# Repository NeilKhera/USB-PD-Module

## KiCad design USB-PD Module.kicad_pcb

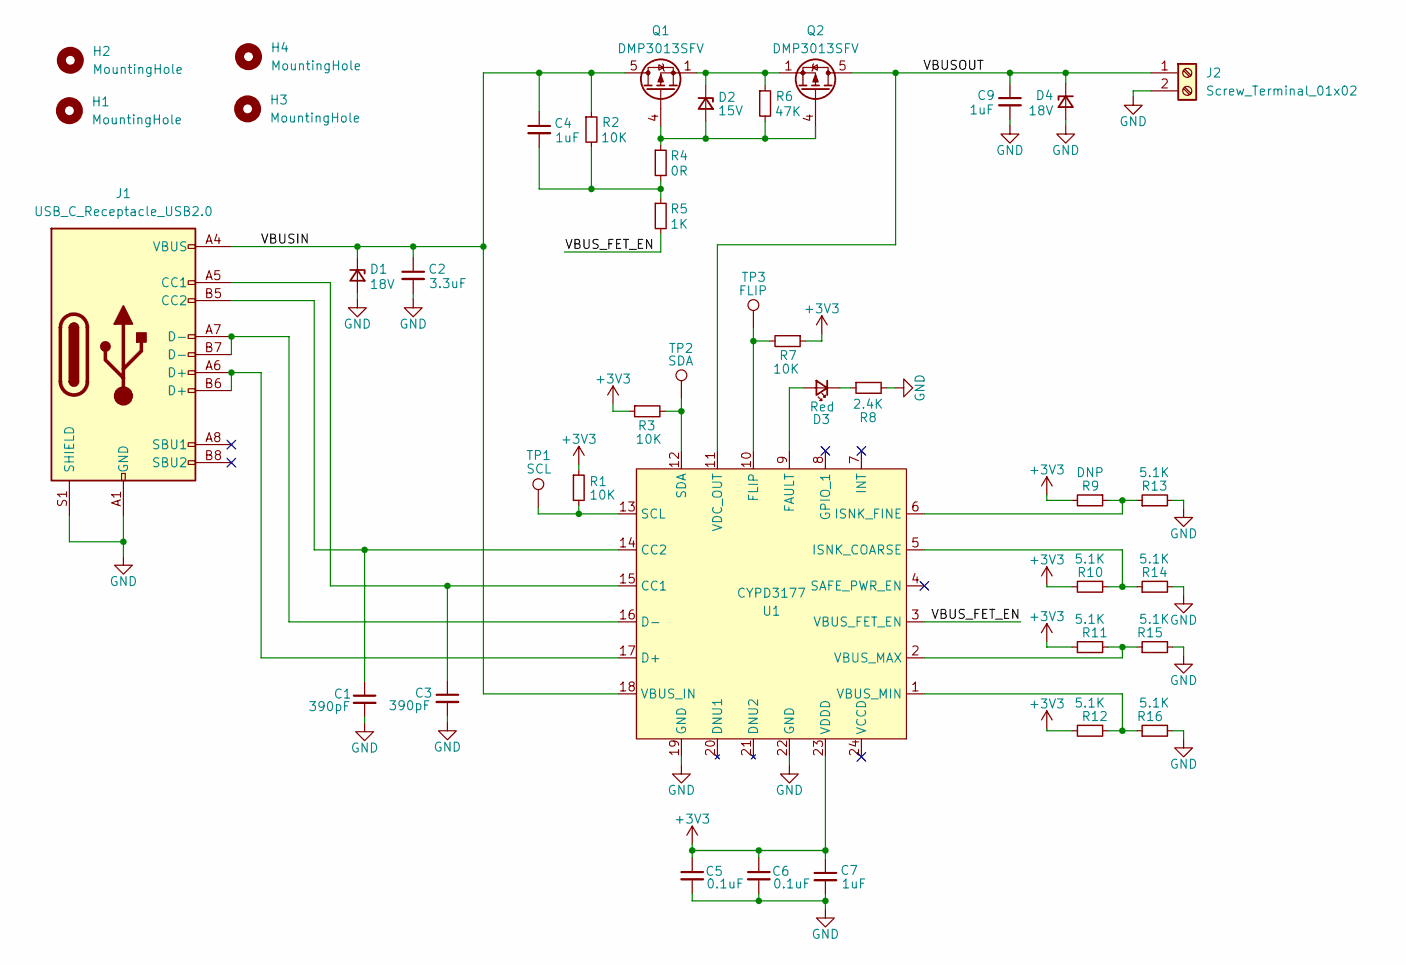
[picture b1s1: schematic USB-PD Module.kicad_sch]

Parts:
C1, C3: 390pF; C_0603_1608Metric
C2: 3.3uF; C_0805_2012Metric
C4, C7: 1uF; C_0603_1608Metric
C5, C6: 0.1uF; C_0603_1608Metric
C9: 1uF; C_0805_2012Metric
D1, D4: 18V; D_SOD-123
D2: 15V; D_SOD-123
D3: Red; LED_0603_1608Metric
H1, H2, H3, H4: MountingHole; MountingHole_2.2mm_M2
J1: USB_C_Receptacle_USB2.0; USB_C_Receptacle_HRO_TYPE-C-31-M-12
J2: Screw_Terminal_01x02; PinHeader_2x01_P2.54mm_Vertical
Q1, Q2: DMP3013SFV; Diodes_PowerDI3333-8
R1, R2, R3, R7: 10K; R_0603_1608Metric
R4: 0R; R_0603_1608Metric
R5: 1K; R_0603_1608Metric
R6: 47K; R_0603_1608Metric
R8: 2.4K; R_0603_1608Metric
R9: DNP; R_0603_1608Metric
R10, R11, R12, R13, R14, R15, R16: 5.1K; R_0603_1608Metric
TP1: SCL; TestPoint_Pad_D1.5mm
TP2: SDA; TestPoint_Pad_D1.5mm
TP3: FLIP; TestPoint_Pad_D1.5mm
U1: CYPD3177; QFN50P400X400X60-25N-D

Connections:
+3V3: C5.1, C6.1, C7.1, R1.1, R3.1, R7.1, R9.2, R10.2, R11.2, R12.2, U1.23 (VDDD)
/VBUSIN: C2.1, C4.1, D1.1 (K), J1.A4 (VBUS), J1.A9 (VBUS), J1.B4 (VBUS), J1.B9 (VBUS), Q1.5 (D), R2.1, U1.18 (VBUS_IN)
/VBUSOUT: C9.1, D4.1 (K), J2.1, Q2.5 (D), U1.11 (VDC_OUT)
/VBUS_FET_EN: R5.2, U1.3 (VBUS_FET_EN)
GND: C1.2, C2.2, C3.2, C5.2, C6.2, C7.2, C9.2, D1.2 (A), D4.2 (A), J1.A1 (GND), J1.A12 (GND), J1.B1 (GND), J1.B12 (GND), J1.S1 (SHIELD), J2.2, R8.2, R13.2, R14.2, R15.2, R16.2, U1.19 (GND), U1.22 (GND), U1.25 (GND)
unnamed: C1.1, J1.B5 (CC2), U1.14 (CC2)
unnamed: C3.1, J1.A5 (CC1), U1.15 (CC1)
unnamed: C4.2, R2.2, R4.2, R5.1
unnamed: D2.1 (K), Q1.1 (S), Q1.2 (S), Q1.3 (S), Q2.1 (S), Q2.2 (S), Q2.3 (S), R6.1
unnamed: D2.2 (A), Q1.4 (G), Q2.4 (G), R4.1, R6.2
unnamed: D3.1 (K), R8.1
unnamed: D3.2 (A), U1.9 (FAULT)
unnamed: J1.A6 (D+), J1.B6 (D+), U1.17 (D+)
unnamed: J1.A7 (D-), J1.B7 (D-), U1.16 (D-)
unnamed: R1.2, TP1.1, U1.13 (SCL)
unnamed: R3.2, TP2.1, U1.12 (SDA)
unnamed: R7.2, TP3.1, U1.10 (FLIP)
unnamed: R10.1, R14.1, U1.5 (ISNK_COARSE)
unnamed: R11.1, R15.1, U1.2 (VBUS_MAX)
unnamed: R12.1, R16.1, U1.1 (VBUS_MIN)
unnamed: R9.1, R13.1, U1.6 (ISNK_FINE)

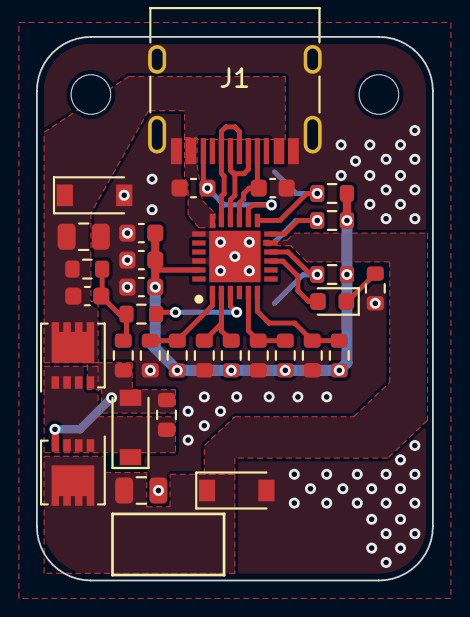
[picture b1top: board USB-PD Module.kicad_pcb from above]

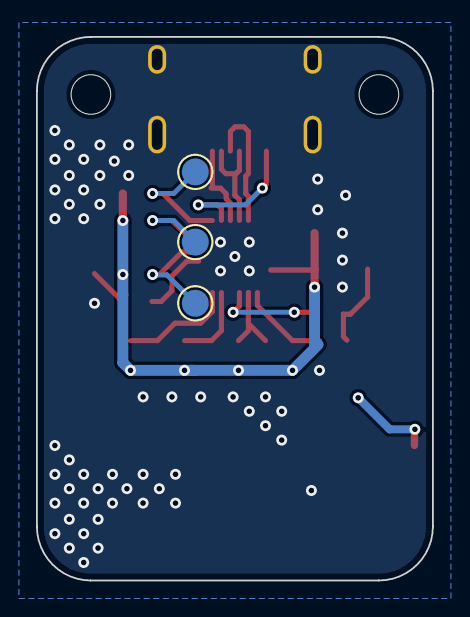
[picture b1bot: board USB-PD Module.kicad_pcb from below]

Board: 2 copper layers, 22.0 x 30.2 mm, 37 parts (3 on the bottom side), 21 nets.

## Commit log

2023-06-20 File upload
2023-06-20 Moved 3D models to their own folder
